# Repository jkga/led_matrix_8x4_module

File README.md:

# LED Matrix(8x4) Module
This repository aims to provide a basic program, schematic diagram, and PCB design for  an eight by four (8x4) LED matrix with Arduino and SN74HC595 shift register IC

## Sketch & Pin Configurations
> [Arduino Uno Sketch](./src/led_8x4.ino)

|                     | Module | Arduino 
| ------------------  | ------ | ------- 
| Latch               | L      | 8 
| Serial Data Input   | D      | 11 
| Clock Input         | C      | 12 
| Row 1               | 4      | 4 
| Row 2               | 3      | 5
| Row 3               | 2      | 6
| Row 4               | 1      | 7
| Power (+)           | +      | 5v
| Power (-)           | -      | GND

## Bills of Materials

| QTY       | Reference   | Value 
| --------  | ----------- | --------- 
| 1         | C1          | 33uf        
| 1         | C2          | 0.1uf       
| 1         | C3          | 0.1uf   
| 32        | D1 - D32    | LED (Vfmin = 1.7v; Ifmax = 0.25mA)  
| 1         | J1          | 1x4 Female Connector  
| 1         | J2          | 1x4 Female Connector  
| 1         | J3          | 1x4 Female Connector   
| 1         | J4          | 2x8 DIP Socket  
| 8         | Q1 - Q8     | PN2222A BJT Transistor
| 8         |             | 4.7k ohms
| 8         |             | 510 ohms
| 1         | U1          | SN74HC595N  
| 10        |             | Jumper Wires 

## Demo
> L.O.V.E - A Valentine's day message to everyone   

https://user-images.githubusercontent.com/10413754/155494353-f9fd05cc-bb8c-47e1-8aa6-f02e38358166.mp4

## Schematic Diagram

## Printed Circuit Board

## Rendered Model

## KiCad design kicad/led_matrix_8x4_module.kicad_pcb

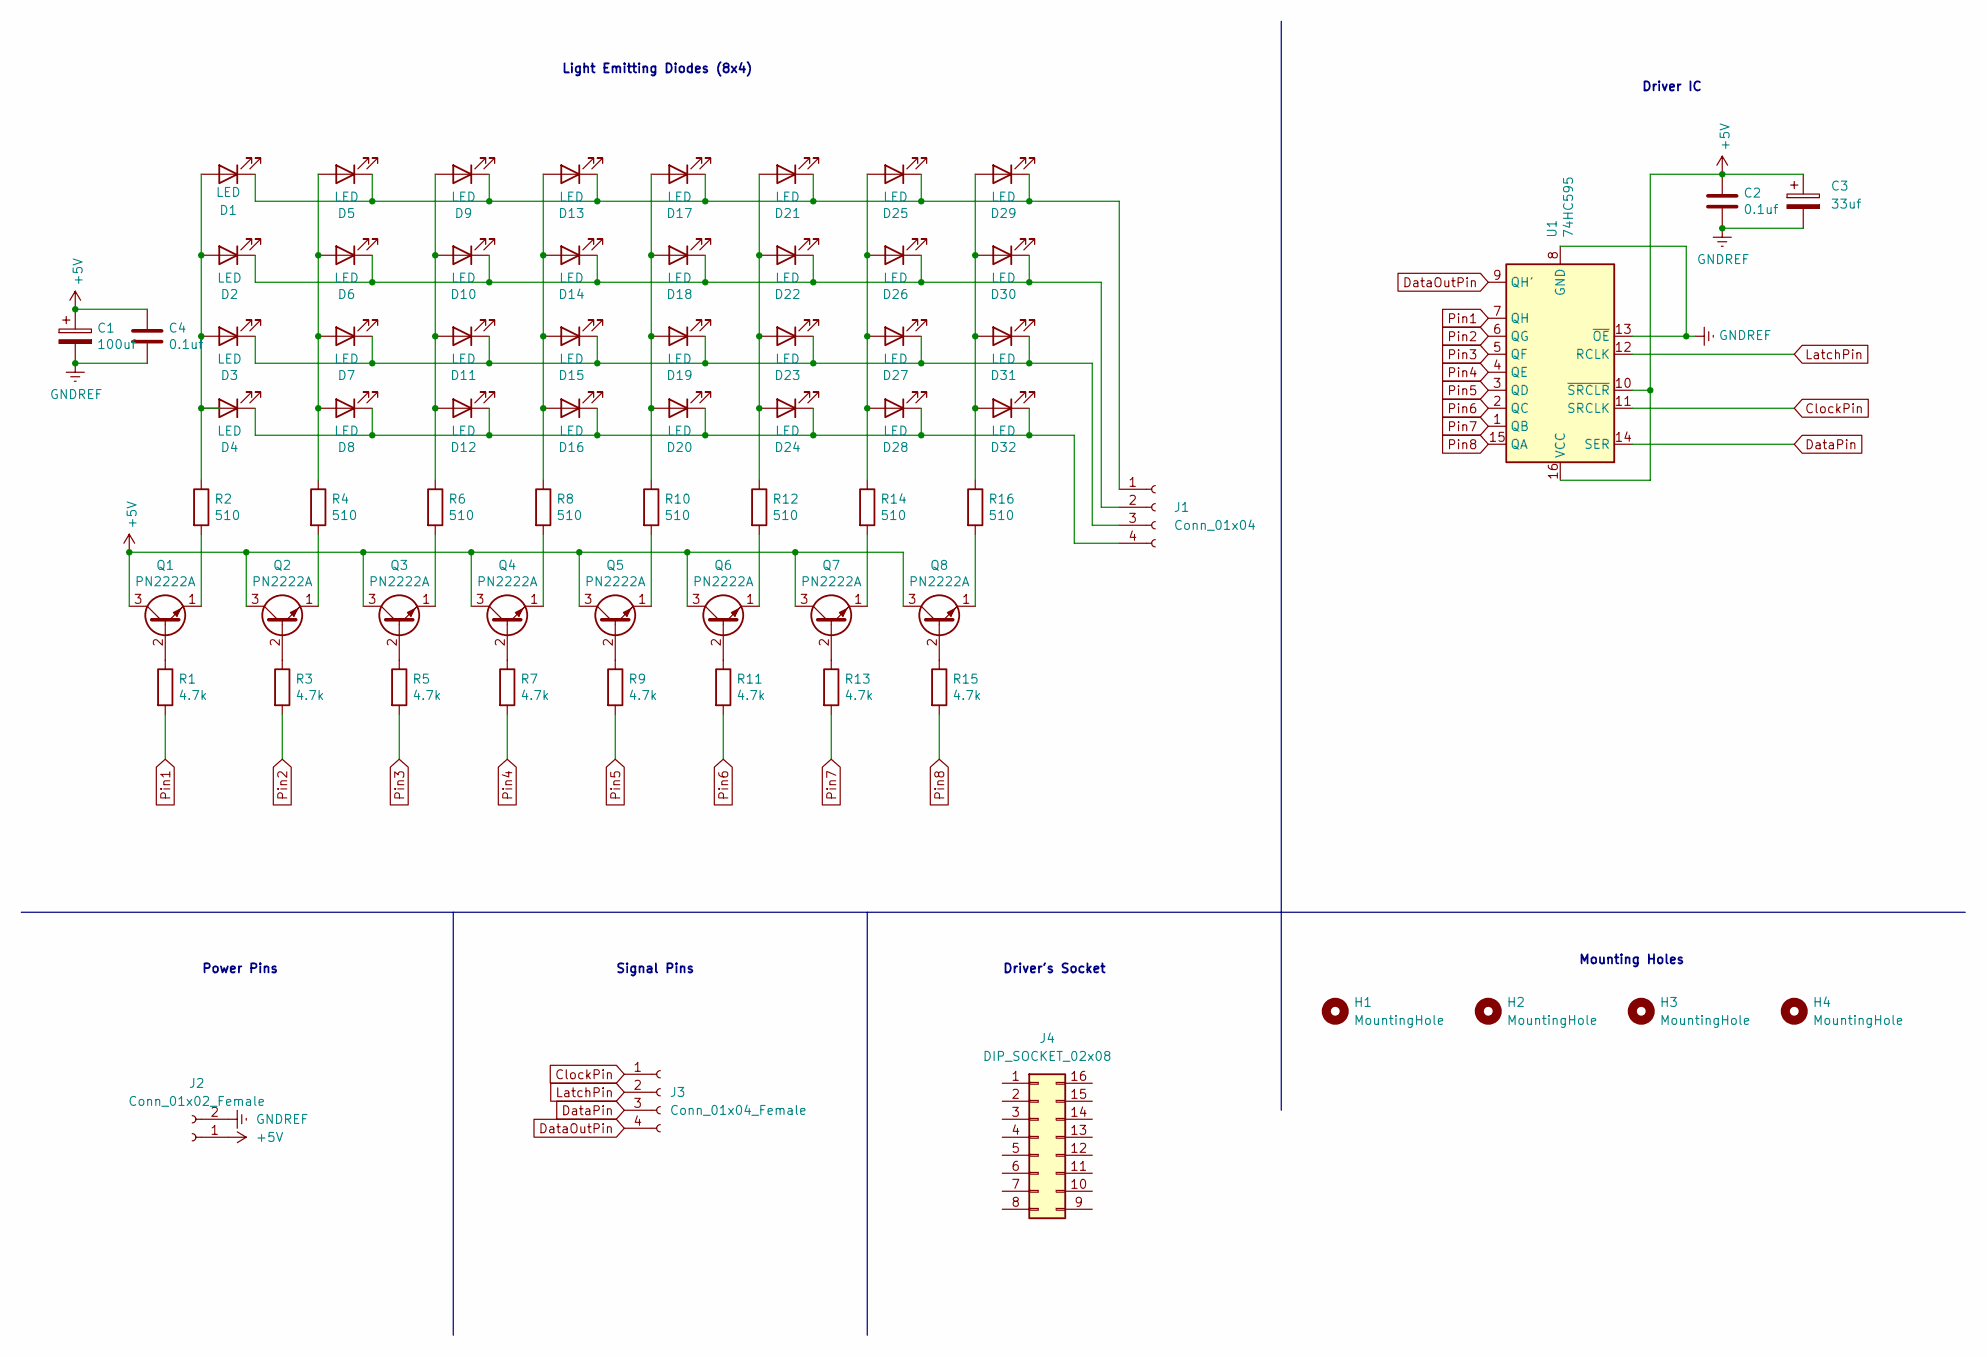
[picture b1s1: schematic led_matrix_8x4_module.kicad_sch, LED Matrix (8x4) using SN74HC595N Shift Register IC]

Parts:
C1: 100uf; CP_Radial_D5.0mm_P2.00mm
C2, C4: 0.1uf; C_Disc_D3.0mm_W1.6mm_P2.50mm
C3: 33uf; CP_Radial_D4.0mm_P1.50mm
D1, D2, D3, D4, D5, D6, D7, D8, D9, D10, D11, D12, D13, D14, D15, D16, D17, D18, D19, D20, D21, D22, D23, D24, D25, D26, D27, D28, D29, D30, D31, D32: LED; LED_D5.0mm
H1, H2, H3, H4: MountingHole; MountingHole_2.2mm_M2_Pad_Via
J1: Conn_01x04; PinHeader_1x04_P2.00mm_Horizontal
J2: Conn_01x02_Female; PinHeader_1x02_P2.00mm_Horizontal
J3: Conn_01x04_Female; PinHeader_1x04_P2.00mm_Horizontal
J4: DIP_SOCKET_02x08; DIP-16_W7.62mm_Socket
Q1, Q2, Q3, Q4, Q5, Q6, Q7, Q8: PN2222A; TO-92_Inline
R1, R3, R5, R7, R9, R11, R13, R15: 4.7k; R_Axial_DIN0204_L3.6mm_D1.6mm_P5.08mm_Horizontal
R2, R4, R6, R8, R10, R12, R14, R16: 510; R_Axial_DIN0204_L3.6mm_D1.6mm_P5.08mm_Horizontal
U1: 74HC595; DIP-16_W7.62mm

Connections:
+5V: C1.1, C2.1, C3.1, C4.1, J2.1, Q1.3 (C), Q2.3 (C), Q3.3 (C), Q4.3 (C), Q5.3 (C), Q6.3 (C), Q7.3 (C), Q8.3 (C), U1.10 (~SRCLR), U1.16 (VCC)
ClockPin: J3.1, U1.11 (SRCLK)
DataOutPin: J3.4, U1.9 (QH')
DataPin: J3.3, U1.14 (SER)
GNDREF: C1.2, C2.2, C3.2, C4.2, J2.2, U1.8 (GND), U1.13 (~OE)
LatchPin: J3.2, U1.12 (RCLK)
unnamed: D1.1 (K), D5.1 (K), D9.1 (K), D13.1 (K), D17.1 (K), D21.1 (K), D25.1 (K), D29.1 (K), J1.1
unnamed: D1.2 (A), D2.2 (A), D3.2 (A), D4.2 (A), R2.1
unnamed: D5.2 (A), D6.2 (A), D7.2 (A), D8.2 (A), R4.1
unnamed: D2.1 (K), D6.1 (K), D10.1 (K), D14.1 (K), D18.1 (K), D22.1 (K), D26.1 (K), D30.1 (K), J1.2
unnamed: D9.2 (A), D10.2 (A), D11.2 (A), D12.2 (A), R6.1
unnamed: D3.1 (K), D7.1 (K), D11.1 (K), D15.1 (K), D19.1 (K), D23.1 (K), D27.1 (K), D31.1 (K), J1.3
unnamed: D4.1 (K), D8.1 (K), D12.1 (K), D16.1 (K), D20.1 (K), D24.1 (K), D28.1 (K), D32.1 (K), J1.4
unnamed: D13.2 (A), D14.2 (A), D15.2 (A), D16.2 (A), R8.1
unnamed: D17.2 (A), D18.2 (A), D19.2 (A), D20.2 (A), R10.1
unnamed: D21.2 (A), D22.2 (A), D23.2 (A), D24.2 (A), R12.1
unnamed: D25.2 (A), D26.2 (A), D27.2 (A), D28.2 (A), R14.1
unnamed: D29.2 (A), D30.2 (A), D31.2 (A), D32.2 (A), R16.1
unnamed: Q1.1 (E), R2.2
unnamed: Q1.2 (B), R1.1
unnamed: Q2.1 (E), R4.2
unnamed: Q2.2 (B), R3.1
unnamed: Q3.1 (E), R6.2
unnamed: Q3.2 (B), R5.1
unnamed: Q4.1 (E), R8.2
unnamed: Q4.2 (B), R7.1
unnamed: Q5.1 (E), R10.2
unnamed: Q5.2 (B), R9.1
unnamed: Q6.1 (E), R12.2
unnamed: Q6.2 (B), R11.1
unnamed: Q7.1 (E), R14.2
unnamed: Q7.2 (B), R13.1
unnamed: Q8.1 (E), R16.2
unnamed: Q8.2 (B), R15.1
Pin1: R1.2, U1.7 (QH)
Pin2: R3.2, U1.6 (QG)
Pin3: R5.2, U1.5 (QF)
Pin4: R7.2, U1.4 (QE)
Pin5: R9.2, U1.3 (QD)
Pin6: R11.2, U1.2 (QC)
Pin7: R13.2, U1.1 (QB)
Pin8: R15.2, U1.15 (QA)

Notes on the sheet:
Driver IC
Light Emitting Diodes (8x4)
Mounting Holes
Driver's Socket
Power Pins
Signal Pins

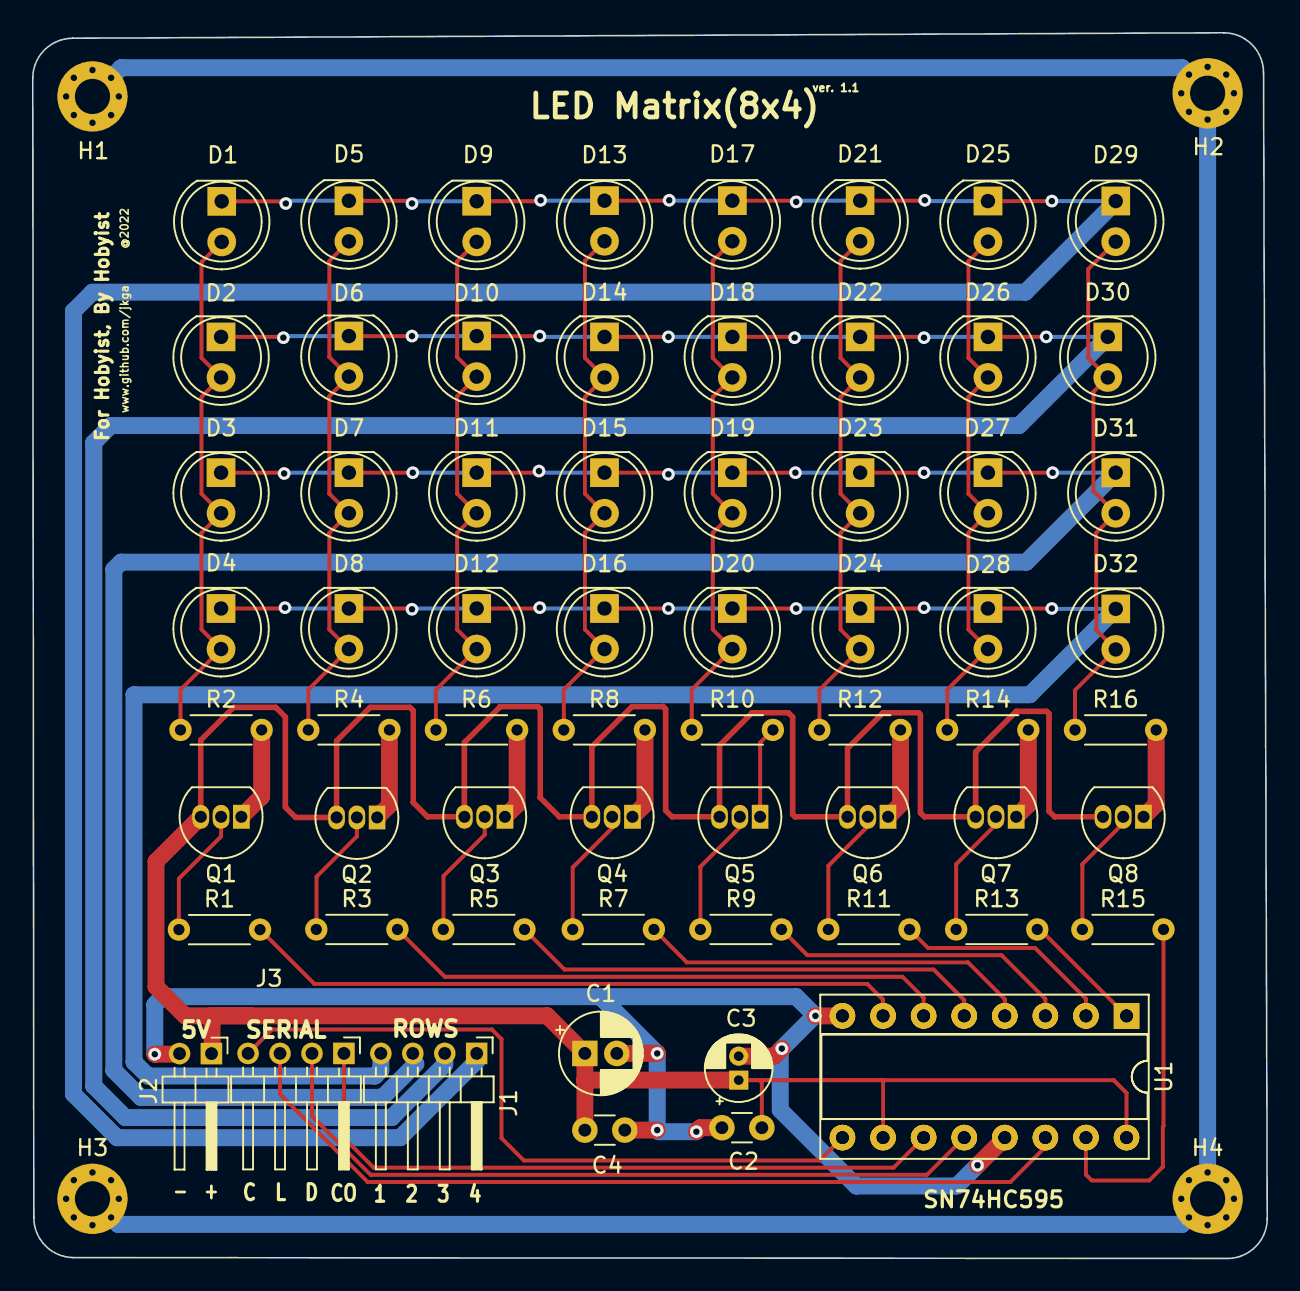
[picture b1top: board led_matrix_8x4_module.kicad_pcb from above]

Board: 2 copper layers, 77.3 x 76.7 mm, 69 parts (0 on the bottom side), 42 nets.

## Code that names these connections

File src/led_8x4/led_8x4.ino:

//74HC595N pins
#define latchPin 8
#define dataPin 11
#define clockPin 12

//vertical pins
#define row1Pin 4
#define row2Pin 5
#define row3Pin 6
#define row4Pin 7

const char pins[] = {
  row1Pin,
  row2Pin,
  row3Pin,
  row4Pin
};


//characters in binary
unsigned int charA[4][8] = {
  {0,0,0,1,1,0,0,0},
  {0,0,1,0,0,1,0,0},
  {0,0,1,1,1,1,0,0},
  {0,0,1,0,0,1,0,0}
};

unsigned int charB[4][8] = {
  {0,0,1,1,1,1,0,0},
  {0,0,1,0,1,1,0,0},
  {0,0,1,1,0,1,0,0},
  {0,0,1,1,1,1,0,0}
};

unsigned  int charC[4][8] = {
  {0,0,1,1,1,1,0,0},
  {0,0,1,0,0,0,0,0},
  {0,0,1,0,0,0,0,0},
  {0,0,1,1,1,1,0,0}
};

unsigned int charD[4][8] = {
  {0,0,1,1,1,0,0,0},
  {0,0,1,0,0,1,0,0},
  {0,0,1,0,0,1,0,0},
  {0,0,1,1,1,0,0,0}
};

unsigned int charE[4][8] = {
  {0,0,1,1,1,1,0,0},
  {0,0,1,1,1,1,0,0},
  {0,0,1,0,0,0,0,0},
  {0,0,1,1,1,1,0,0}
};

unsigned int charF[4][8] = {
  {0,0,1,1,1,1,0,0},
  {0,0,1,0,0,0,0,0},
  {0,0,1,1,1,1,0,0},
  {0,0,1,0,0,0,0,0}
};

unsigned int charG[4][8] = {
  {0,0,0,1,1,0,0,0},
  {0,0,1,0,0,0,0,0},
  {0,0,1,0,1,1,0,0},
  {0,0,1,1,1,1,0,0}
};

unsigned int charH[4][8] = {
  {0,0,1,0,0,1,0,0},
  {0,0,1,1,1,1,0,0},
  {0,0,1,1,1,1,0,0},
  {0,0,1,0,0,1,0,0}
};

unsigned int charI[4][8] = {
  {0,0,1,1,1,1,0,0},
  {0,0,0,1,1,0,0,0},
  {0,0,0,1,1,0,0,0},
  {0,0,1,1,1,1,0,0}
};

unsigned int charJ[4][8] = {
  {0,0,0,0,0,1,0,0},
  {0,0,0,0,0,1,0,0},
  {0,0,1,0,0,1,0,0},
  {0,0,1,1,1,1,0,0}
};

unsigned int charK[4][8] = {
  {0,0,1,0,0,1,0,0},
  {0,0,1,1,1,0,0,0},
  {0,0,1,0,1,0,0,0},
  {0,0,1,0,0,1,0,0}
};

unsigned int charL[4][8] = {
  {0,0,1,0,0,0,0,0},
  {0,0,1,0,0,0,0,0},
  {0,0,1,0,0,0,0,0},
  {0,0,1,1,1,1,0,0}
};

unsigned int charM[4][8] = {
  {0,0,1,0,0,1,0,0},
  {0,0,1,1,1,1,0,0},
  {0,0,1,0,0,1,0,0},
  {0,0,1,0,0,1,0,0}
};

unsigned int charN[4][8] = {
  {0,0,1,0,0,1,0,0},
  {0,0,1,1,0,1,0,0},
  {0,0,1,0,1,1,0,0},
  {0,0,1,0,0,1,0,0}
};

unsigned int charO[4][8] = {
  {0,0,1,1,1,1,0,0},
  {0,0,1,0,0,1,0,0},
  {0,0,1,0,0,1,0,0},
  {0,0,1,1,1,1,0,0}
};

unsigned int charP[4][8] = {
  {0,0,1,1,1,1,0,0},
  {0,0,1,1,1,1,0,0},
  {0,0,1,0,0,0,0,0},
  {0,0,1,0,0,0,0,0}
};

int charQ[4][8] = {
  {0,0,1,1,1,1,0,0},
  {0,0,1,0,0,1,0,0},
  {0,0,1,0,1,1,0,0},
  {0,0,1,1,1,1,0,0}
};

unsigned int charR[4][8] = {
  {0,0,1,1,1,1,0,0},
  {0,0,1,0,1,1,0,0},
  {0,0,1,1,1,0,0,0},
  {0,0,1,0,0,1,0,0}
};

unsigned int charS[4][8] = {
  {0,0,1,1,1,1,0,0},
  {0,0,1,0,0,0,0,0},
  {0,0,0,1,1,1,0,0},
  {0,0,1,1,1,1,0,0}
};

unsigned int charT[4][8] = {
  {0,0,1,1,1,1,0,0},
  {0,0,0,1,1,0,0,0},
  {0,0,0,1,1,0,0,0},
  {0,0,0,1,1,0,0,0}
};

unsigned int charU[4][8] = {
  {0,0,1,0,0,1,0,0},
  {0,0,1,0,0,1,0,0},
  {0,0,1,0,0,1,0,0},
  {0,0,1,1,1,1,0,0}
};

unsigned int charV[4][8] = {
  {0,0,1,0,0,1,0,0},
  {0,0,1,0,0,1,0,0},
  {0,0,1,0,0,1,0,0},
  {0,0,0,1,1,0,0,0}
};

unsigned int charW[4][8] = {
  {0,0,1,0,0,1,0,0},
  {0,0,1,0,0,1,0,0},
  {0,0,1,1,1,1,0,0},
  {0,0,1,0,0,1,0,0}
};

unsigned int charX[4][8] = {
  {0,0,1,0,0,1,0,0},
  {0,0,0,1,1,0,0,0},
  {0,0,0,1,1,0,0,0},
  {0,0,1,0,0,1,0,0}
};

unsigned int charY[4][8] = {
  {0,0,1,0,0,1,0,0},
  {0,0,0,1,1,0,0,0},
  {0,0,0,1,1,0,0,0},
  {0,0,0,1,1,0,0,0}
};

int charZ[4][8] = {
  {0,0,1,1,1,1,0,0},
  {0,0,0,0,1,0,0,0},
  {0,0,0,1,0,0,0,0},
  {0,0,1,1,1,1,0,0}
};

unsigned int charHeart[4][8] = {
  {0,1,1,0,0,1,1,0},
  {0,1,1,1,1,1,1,0},
  {0,0,1,1,1,1,0,0},
  {0,0,0,1,1,0,0,0}
};


unsigned int board8x4[4][8] = {
  {0,0,0,0,0,0,0,0},
  {0,0,0,0,0,0,0,0},
  {0,0,0,0,0,0,0,0},
  {0,0,0,0,0,0,0,0}
};

int binToDec (char *bin) {
   int decVal = 0;
    for (int i=0; i< strlen(bin); i++)
    {
      decVal *= 2;
      if (bin[i] == '1') decVal++;
    }
    return decVal;
}

char* join(int *chars) {
  char* dd = malloc(1);
  char buffer[8];
  for(int x = 0; x < 8; x++) {
    sprintf(buffer, "%d", chars[x]);
    strcat(dd, buffer);
  }
  return dd;
}

int currentRow = 0;
int currentDisplayColumIndex = 0;

unsigned long startMillis;
unsigned long currentMillis;
const unsigned long period = 100;


int displaySingleLetter (int character[][8]) {

    for (int row = 0; row < 4; row++) {

      digitalWrite(latchPin, LOW);
      
      //join array and convert to decimal value
      char *charByte = join(character[row]);
      int val = binToDec(charByte);

      // shift out the bits:
      shiftOut(dataPin, clockPin, LSBFIRST, val);
      //take the latch pin high so the LEDs will light up:
      digitalWrite(latchPin, HIGH);

      //freeup memory
      free(charByte);
        
      //disable y axis
      for(int x = 0; x < 4; x++) {
        if(x != currentRow) {
          pinMode(pins[x], INPUT);
        } else {
          pinMode(pins[currentRow], OUTPUT);
          digitalWrite(pins[currentRow], LOW);
        }
      }
      
      //point to next line 
      currentRow++;
         
      // reset row to zero if reached 4 lines
      if(currentRow >= 4 ) currentRow = 0;
      
      // pause before next row
      delay(5);
    }
    return 0;
}

int writeToColumn8x4Board(int board[4][8], int pos, int rowBits[4]) {

   for(int y = 0; y < 4; y++) {
     // write new data
      board[y][pos] = rowBits[y];
   }
   return 1;
}

int shift8x4BoardToLeft(int board[4][8]) {
   for(int y = 0; y < 4; y++) {
    int temp;
    int next = 0;
    for(int z = 0; z < 8; z++) {
      next = z+1;
      // write new data
      if(next <= 7) {
        temp = board[y][next];
        board[y][z] = temp;
      }
    }
   }
   return 1;
}

int* getColumnOf8x4Character(int chars[4][8], int columnPos) {
  static int rows[4]={0,1,1,0};
  for(int x=0; x < 4; x++) {
    for(int j=0; j<8; j++) {
      if(j==columnPos) rows[x] = chars[x][j];
    }
  } 
  return rows;
}

void setup() {
  //set pins to output
  pinMode(latchPin, OUTPUT);
  pinMode(clockPin, OUTPUT);
  pinMode(dataPin, OUTPUT);
  
  //set pins to high impedance
  pinMode(row1Pin, INPUT);
  pinMode(row2Pin, INPUT);
  pinMode(row3Pin, INPUT);
  pinMode(row4Pin, INPUT);
  startMillis = millis();
}


int letterIndex = 0;

int scrollText(int board8x4, int letters[], int letterCount, int columnCount) {
  int *bits = malloc(1);
  currentMillis = millis();

  if (currentMillis - startMillis >= period)
  {
    //use current time as start time
    startMillis = currentMillis;
    currentDisplayColumIndex++;
    free(bits);

    //point the cursor to the first element in the array of letters
    if(currentDisplayColumIndex > columnCount - 1) {
      letterIndex++;
      currentDisplayColumIndex = 0; 
    }
    if(letterIndex > letterCount - 1) letterIndex = 0;

    shift8x4BoardToLeft(board8x4);
  }

  bits= {getColumnOf8x4Character(letters[letterIndex], currentDisplayColumIndex)};
  int reversedColumnIndex = 7-currentDisplayColumIndex;
  writeToColumn8x4Board(board8x4, 7, bits); 
  displaySingleLetter(board8x4);
}

/*const int letters[] = {
  charA,
  charB,
  charC,
  charD,
  charE,
  charF,
  charG,
  charH,
  charI,
  charJ,
  charK,
  charL,
  charM,
  charN,
  charO,
  charP,
  charQ,
  charR,
  charS,
  charT,
  charU,
  charV,
  charW,
  charX,
  charY,
  charZ,
  charHeart
};*/


  
void loop() {
  const int letters[] = {
    charL,
    charO,
    charV,
    charE,
    charHeart
  };
  scrollText(board8x4, letters, sizeof(letters) / sizeof(int), 8);
}

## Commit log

2022-02-24 feat: add sketch and kicad files
2022-02-24 feat: add demo video
2022-03-02 release: v1.1
2022-03-10 fix: add break in declared variable inside loop
